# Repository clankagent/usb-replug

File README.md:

# USB Replug — revision B

A USB-A male-to-female adapter intended to simulate unplugging and reconnecting a USB 2.0 peripheral with one button press. A CMOS 555 provides the delay; there is no microcontroller or firmware.

**Public design review. Unbuilt prototype; not ready to order.** Assembly placement mappings remain unresolved and hardware performance has not been tested. This repository contains only the current revision B source and review material, not previous design iterations or fabrication releases.

[Schematic PDF](docs/schematic.pdf) · [3D STEP model](docs/usb-replug.step) · [BOM](bom.csv) · [Remaining work](docs/STATUS.md)

## Intended operation

Press the central button to disconnect device VBUS and both data lines, then reconnect automatically. Ground and shields stay connected. The trigger circuit is intended to let the timer expire even when the button remains held down.

| Two-position DIP switch | Approximate off time |
|---|---:|
| Both OFF | 3 seconds |
| Either ON | 2 seconds |
| Both ON | 1 second |

Change the DIP settings while idle. RC tolerance, leakage and capacitor bias affect timing; these are nominal settings, not calibrated delays.

## Open the design

Open `usb-replug.kicad_pro` in KiCad 10. The root schematic links three functional sheets. The PCB, footprints and referenced STEP models are included with project-relative paths. Official symbols are embedded in the schematics; the custom symbol library is under `libraries/`.

The board is 70 × 30 mm with four copper layers and nominal 1.6 mm thickness. Its fabrication target is JLC04161H-7628, outer 1 oz / inner 0.5 oz copper, green mask, white silkscreen and lead-free HASL. The male connector overhangs the PCB edge. A different manufacturer needs a stackup and assembly review.

## Validation

The packaged source was checked with KiCad 10.0.6: no reported ERC, PCB DRC, unconnected-item or schematic-parity findings. Reports and their configured ignored-check lists are included in `docs/checks/`. This is not a claim that every possible rule is enabled or that hardware works.

The intended USB data rate is up to 480 Mbps. Signal integrity, impedance, interoperability, ESD behavior, loaded voltage drop and timing still require review and physical testing. Length matching alone does not validate the USB routing; the layout includes uncoupled breakout sections. A self-powered peripheral may disconnect logically without actually power-cycling. Host power budget includes the adapter's own consumption.

## Assembly and availability

All small components are intended for factory assembly. JLCPCB's quoted Economic option excluded J1, the male connector; it has accessible surface-mount signal joints plus shell mounting joints. J2 is through-hole. The quoted Standard option included both connectors. Historical September 2026 batch estimates were $71.08 and $106.07 respectively for five PCBs with two populated, excluding shipping and tax. These are not current offers or endorsements.

Gerbers and pick-and-place files are deliberately absent: the previous assembler preview exposed rotation and connector-origin mismatches. No order-ready release has been published and no board has been ordered.

## Licensing and provenance

See [THIRD_PARTY.md](THIRD_PARTY.md). Public visibility does not grant an open-source license for the original project; no project license has been selected. Existing third-party licenses remain in effect. Provenance and redistribution permissions for the imported footprints and DIP-switch model remain unresolved; see the linked notes.

Prepared with AI-assisted design and review; the KiCad files, not an image, are the design source of truth.

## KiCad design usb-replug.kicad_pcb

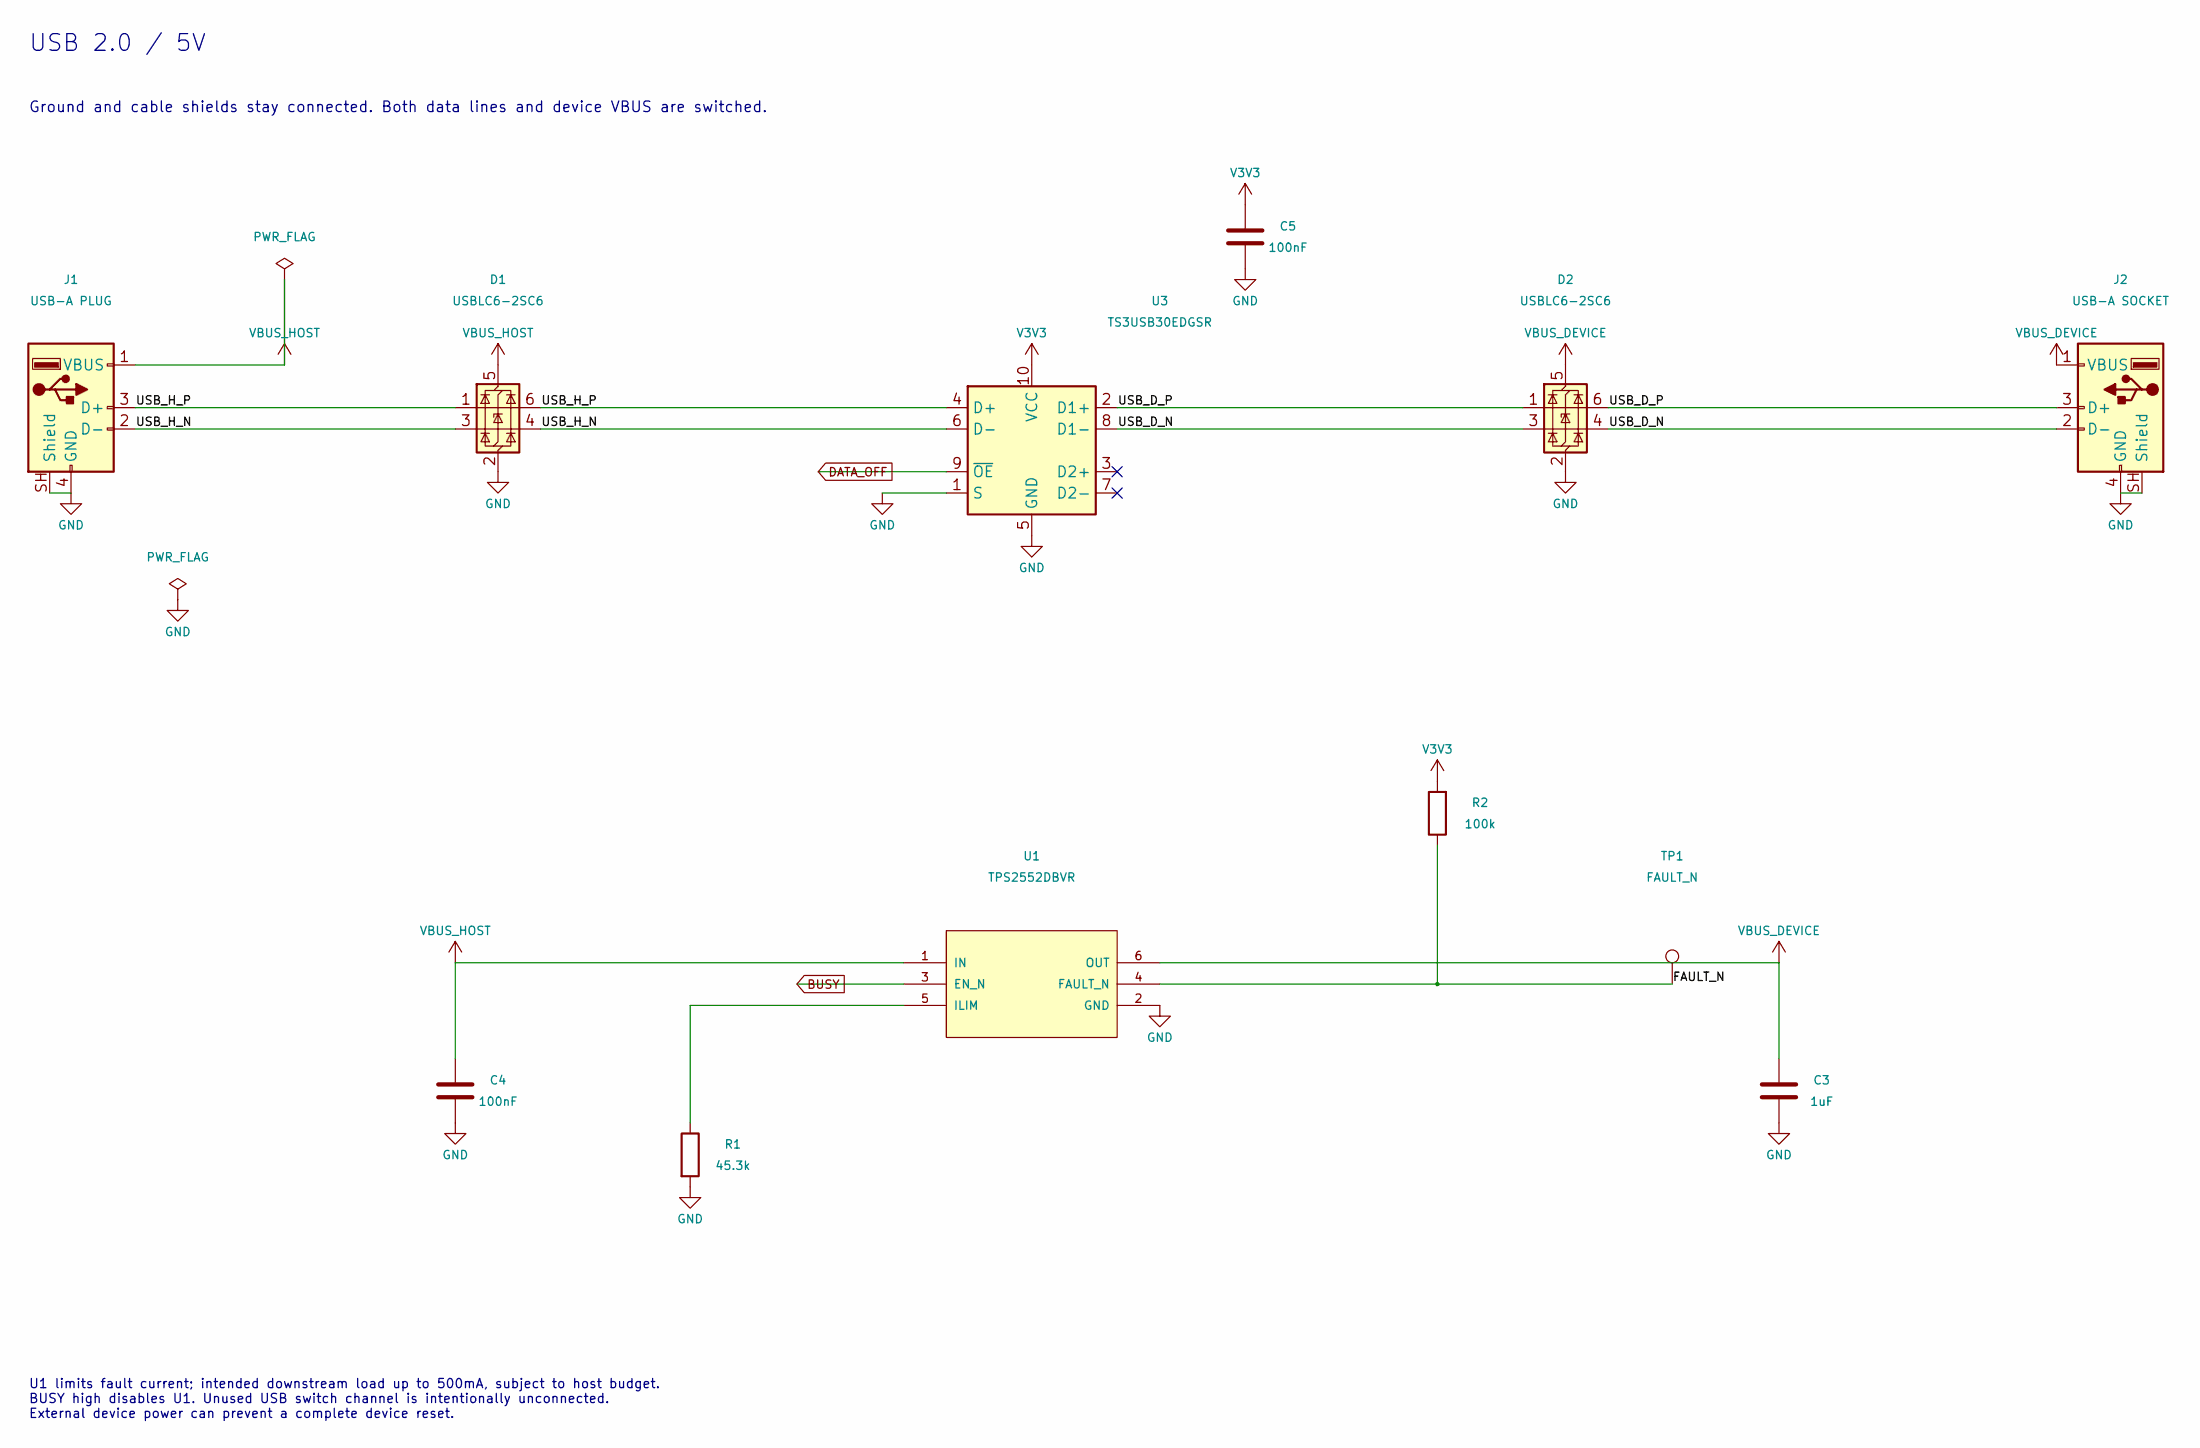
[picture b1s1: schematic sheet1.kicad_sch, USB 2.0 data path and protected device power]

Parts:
C3: 1uF; C_0603_1608Metric; MPN CL10A105KB8NNNC; LCSC C15849
C4, C5: 100nF; C_0603_1608Metric; MPN CC0603KRX7R9BB104; LCSC C14663
D1, D2: USBLC6-2SC6; SOT-23-6; MPN USBLC6-2SC6; LCSC C7519
J1: USB-A PLUG; USB_A_Molex_48037-2200_Horizontal; MPN 480372200; LCSC C2765195
J2: USB-A SOCKET; Jingtuo_902-131A1011D10100; MPN 902-131A1011D10100; LCSC C2345
R1: 45.3k; R_0603_1608Metric; MPN RC0603FR-0745K3L; LCSC C245971
R2: 100k; R_0603_1608Metric; MPN 0603WAF1003T5E; LCSC C25803
TP1: FAULT_N; TestPoint_Pad_D1.5mm; MPN PCB pad
U1: TPS2552DBVR; SOT-23-6; MPN TPS2552DBVR; LCSC C46506
U3: TS3USB30EDGSR; MSOP-10_3x3mm_P0.5mm; MPN TS3USB30EDGSR; LCSC C131998

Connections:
/USB and protected power/FAULT_N: R2.1, TP1.1, U1.4 (FAULT_N)
/USB and protected power/USB_D_N: D2.3 (I/O2), D2.4 (I/O2), J2.2 (D-), U3.8 (D1-)
/USB and protected power/USB_D_P: D2.1 (I/O1), D2.6 (I/O1), J2.3 (D+), U3.2 (D1+)
/USB and protected power/USB_H_N: D1.3 (I/O2), D1.4 (I/O2), J1.2 (D-), U3.6 (D-)
/USB and protected power/USB_H_P: D1.1 (I/O1), D1.6 (I/O1), J1.3 (D+), U3.4 (D+)
BUSY: U1.3 (EN_N); also elsewhere on the board
DATA_OFF: U3.9 (~OE); also elsewhere on the board
GND: C3.2, C4.2, C5.2, D1.2 (GND), D2.2 (GND), J1.4 (GND), J1.SH (Shield), J2.4 (GND), J2.SH (Shield), R1.2, U1.2 (GND), U3.1 (S), U3.5 (GND); also elsewhere on the board
unnamed: R1.1, U1.5 (ILIM)
V3V3: C5.1, R2.2, U3.10 (VCC); also elsewhere on the board
VBUS_DEVICE: C3.1, D2.5 (VBUS), J2.1 (VBUS), U1.6 (OUT); also elsewhere on the board
VBUS_HOST: C4.1, D1.5 (VBUS), J1.1 (VBUS), U1.1 (IN); also elsewhere on the board

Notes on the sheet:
USB 2.0 / 5V
Ground and cable shields stay connected. Both data lines and device VBUS are switched.
U1 limits fault current; intended downstream load up to 500mA, subject to host budget. BUSY high disables U1. Unused USB switch channel is intentionally unconnected. External device power can prevent a complete device reset.

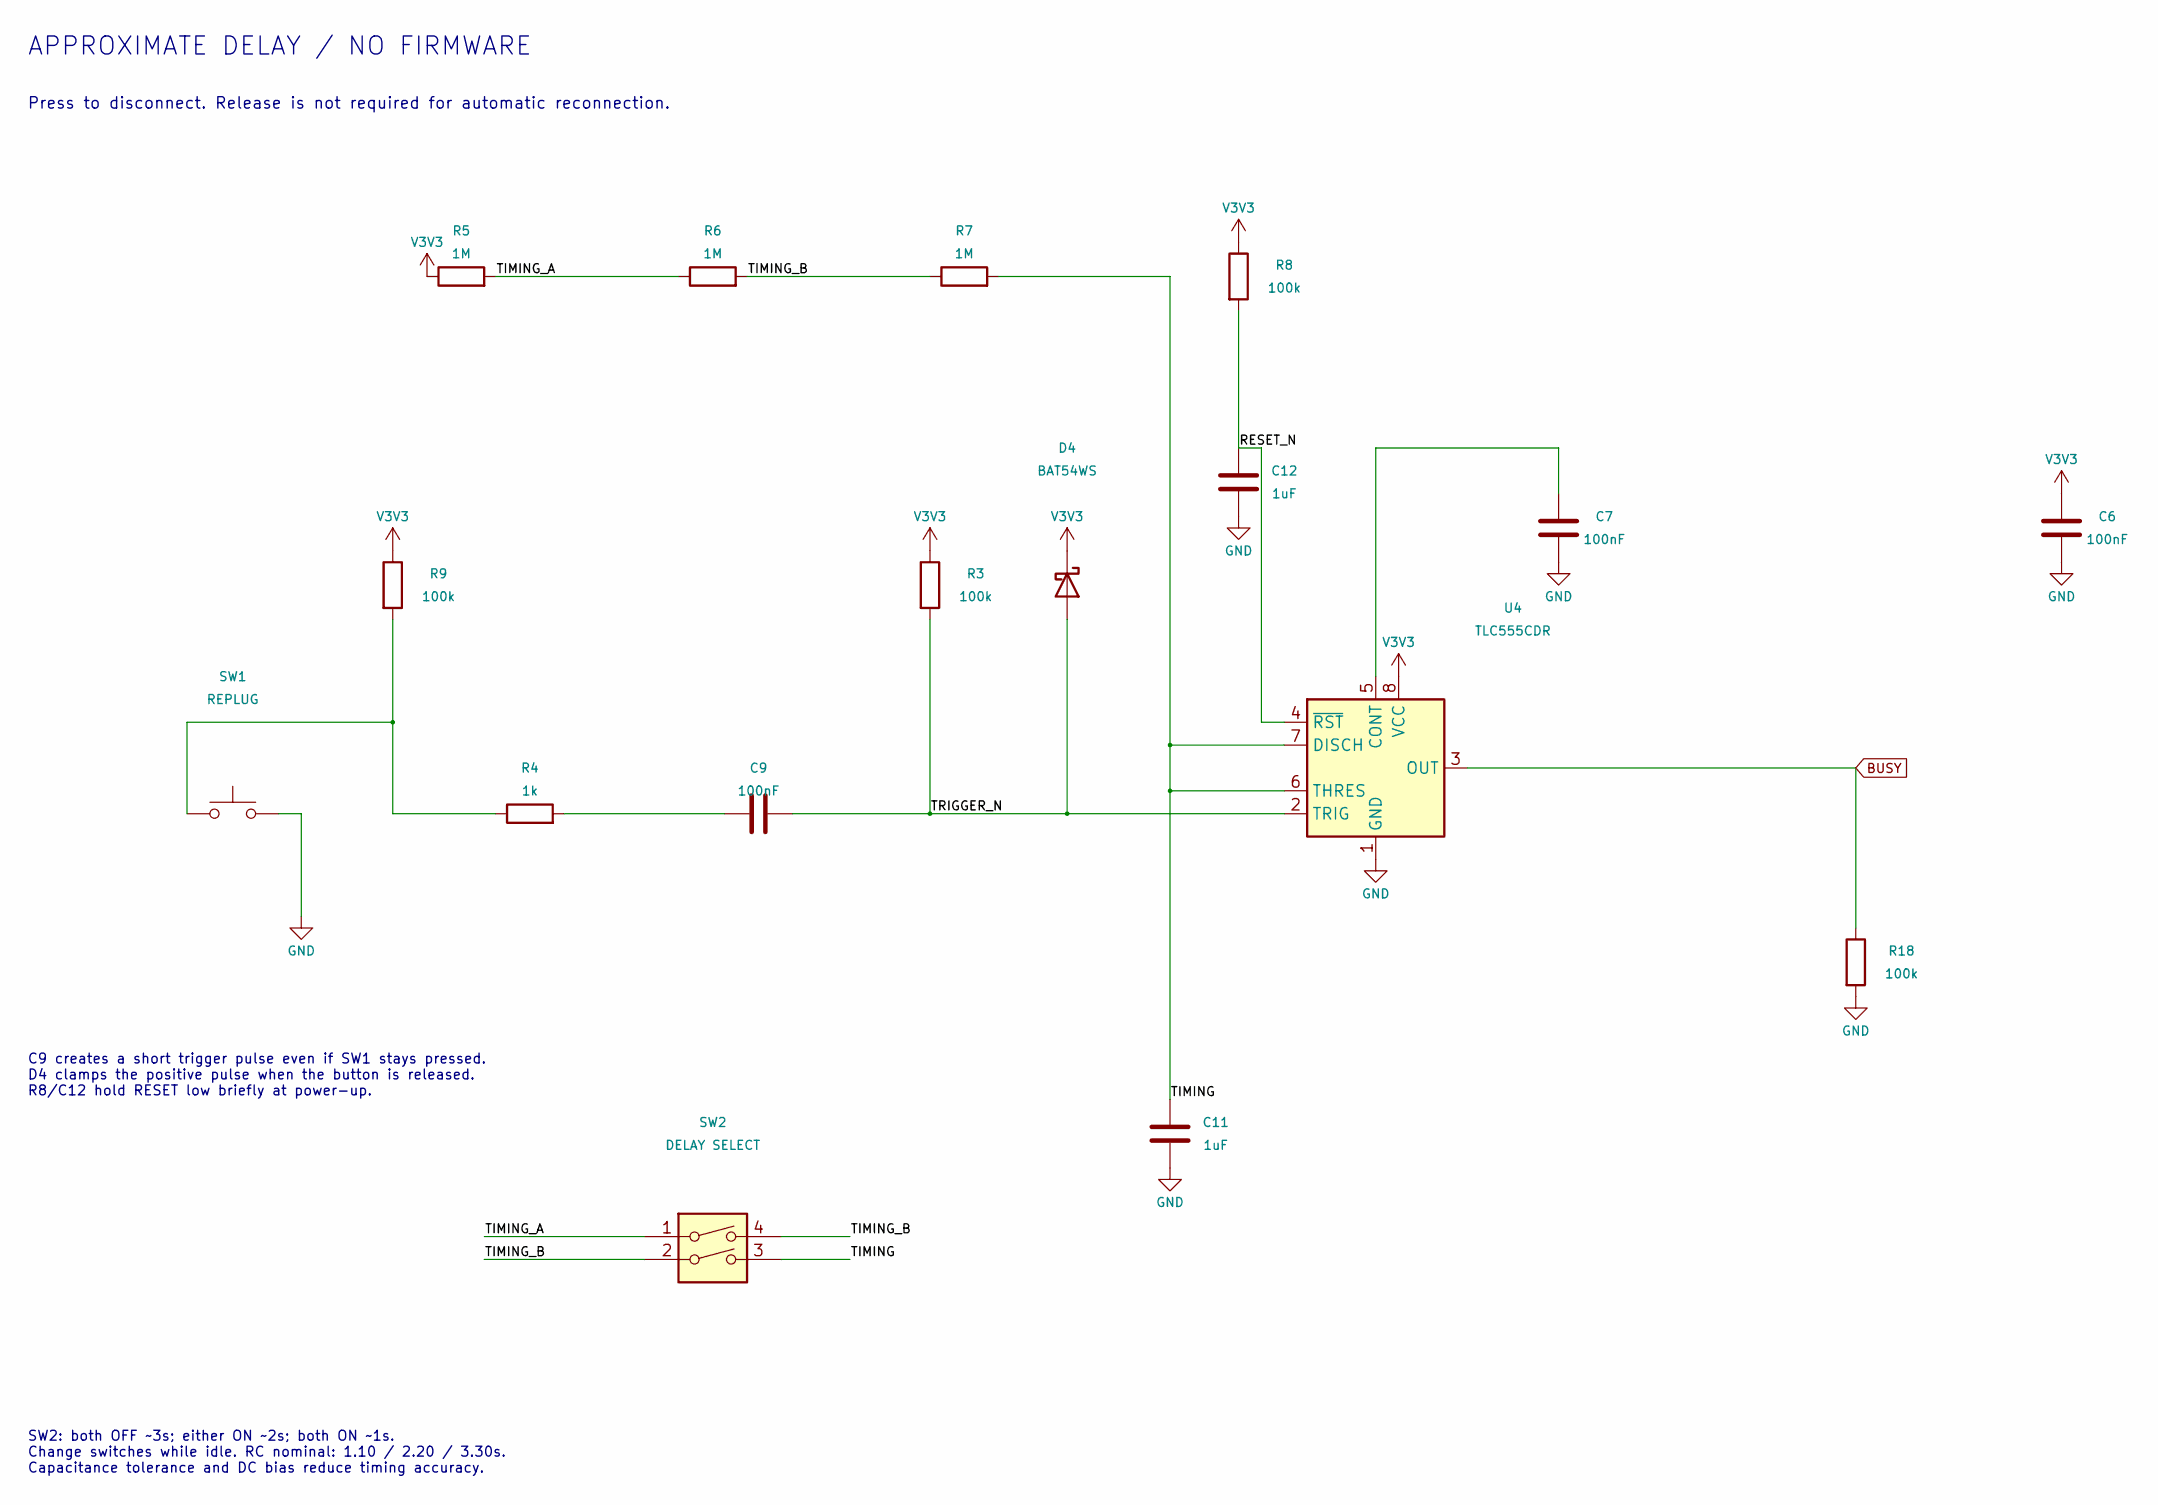
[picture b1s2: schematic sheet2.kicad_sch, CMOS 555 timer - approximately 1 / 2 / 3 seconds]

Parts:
C6, C7, C9: 100nF; C_0603_1608Metric; MPN CC0603KRX7R9BB104; LCSC C14663
C11, C12: 1uF; C_0603_1608Metric; MPN CL10A105KB8NNNC; LCSC C15849
D4: BAT54WS; D_SOD-323; MPN BAT54WS-7-F; LCSC C124205
R3, R8, R9, R18: 100k; R_0603_1608Metric; MPN 0603WAF1003T5E; LCSC C25803
R4: 1k; R_0603_1608Metric; MPN 0603WAF1001T5E; LCSC C21190
R5, R6, R7: 1M; R_0603_1608Metric; MPN 0603WAF1004T5E; LCSC C22935
SW1: REPLUG; SW_SPST_PTS645Sx43SMTR92; MPN PTS645SM43SMTR92 LFS; LCSC C221880
SW2: DELAY SELECT; SHOUHAN_1.27-2P_TPPT; MPN 1.27-2P TPPT; LCSC C7421516
U4: TLC555CDR; SOIC-8_3.9x4.9mm_P1.27mm; MPN TLC555CDR; LCSC C6986

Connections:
/555 hardware timer/RESET_N: C12.1, R8.2, U4.4 (~RST)
/555 hardware timer/TIMING: C11.1, R7.2, SW2.3, U4.6 (THRES), U4.7 (DISCH)
/555 hardware timer/TIMING_A: R5.2, R6.1, SW2.1
/555 hardware timer/TIMING_B: R6.2, R7.1, SW2.2, SW2.4
/555 hardware timer/TRIGGER_N: C9.2, D4.2 (A), R3.2, U4.2 (TRIG)
BUSY: R18.1, U4.3 (OUT); also elsewhere on the board
GND: C6.2, C7.2, C11.2, C12.2, R18.2, SW1.2, U4.1 (GND); also elsewhere on the board
unnamed: C9.1, R4.2
unnamed: R4.1, R9.2, SW1.1
unnamed: C7.1, U4.5 (CONT)
V3V3: C6.1, D4.1 (K), R3.1, R5.1, R8.1, R9.1, U4.8 (VCC); also elsewhere on the board

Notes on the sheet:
APPROXIMATE DELAY / NO FIRMWARE
Press to disconnect. Release is not required for automatic reconnection.
SW2: both OFF ~3s; either ON ~2s; both ON ~1s. Change switches while idle. RC nominal: 1.10 / 2.20 / 3.30s. Capacitance tolerance and DC bias reduce timing accuracy.
C9 creates a short trigger pulse even if SW1 stays pressed. D4 clamps the positive pulse when the button is released. R8/C12 hold RESET low briefly at power-up.

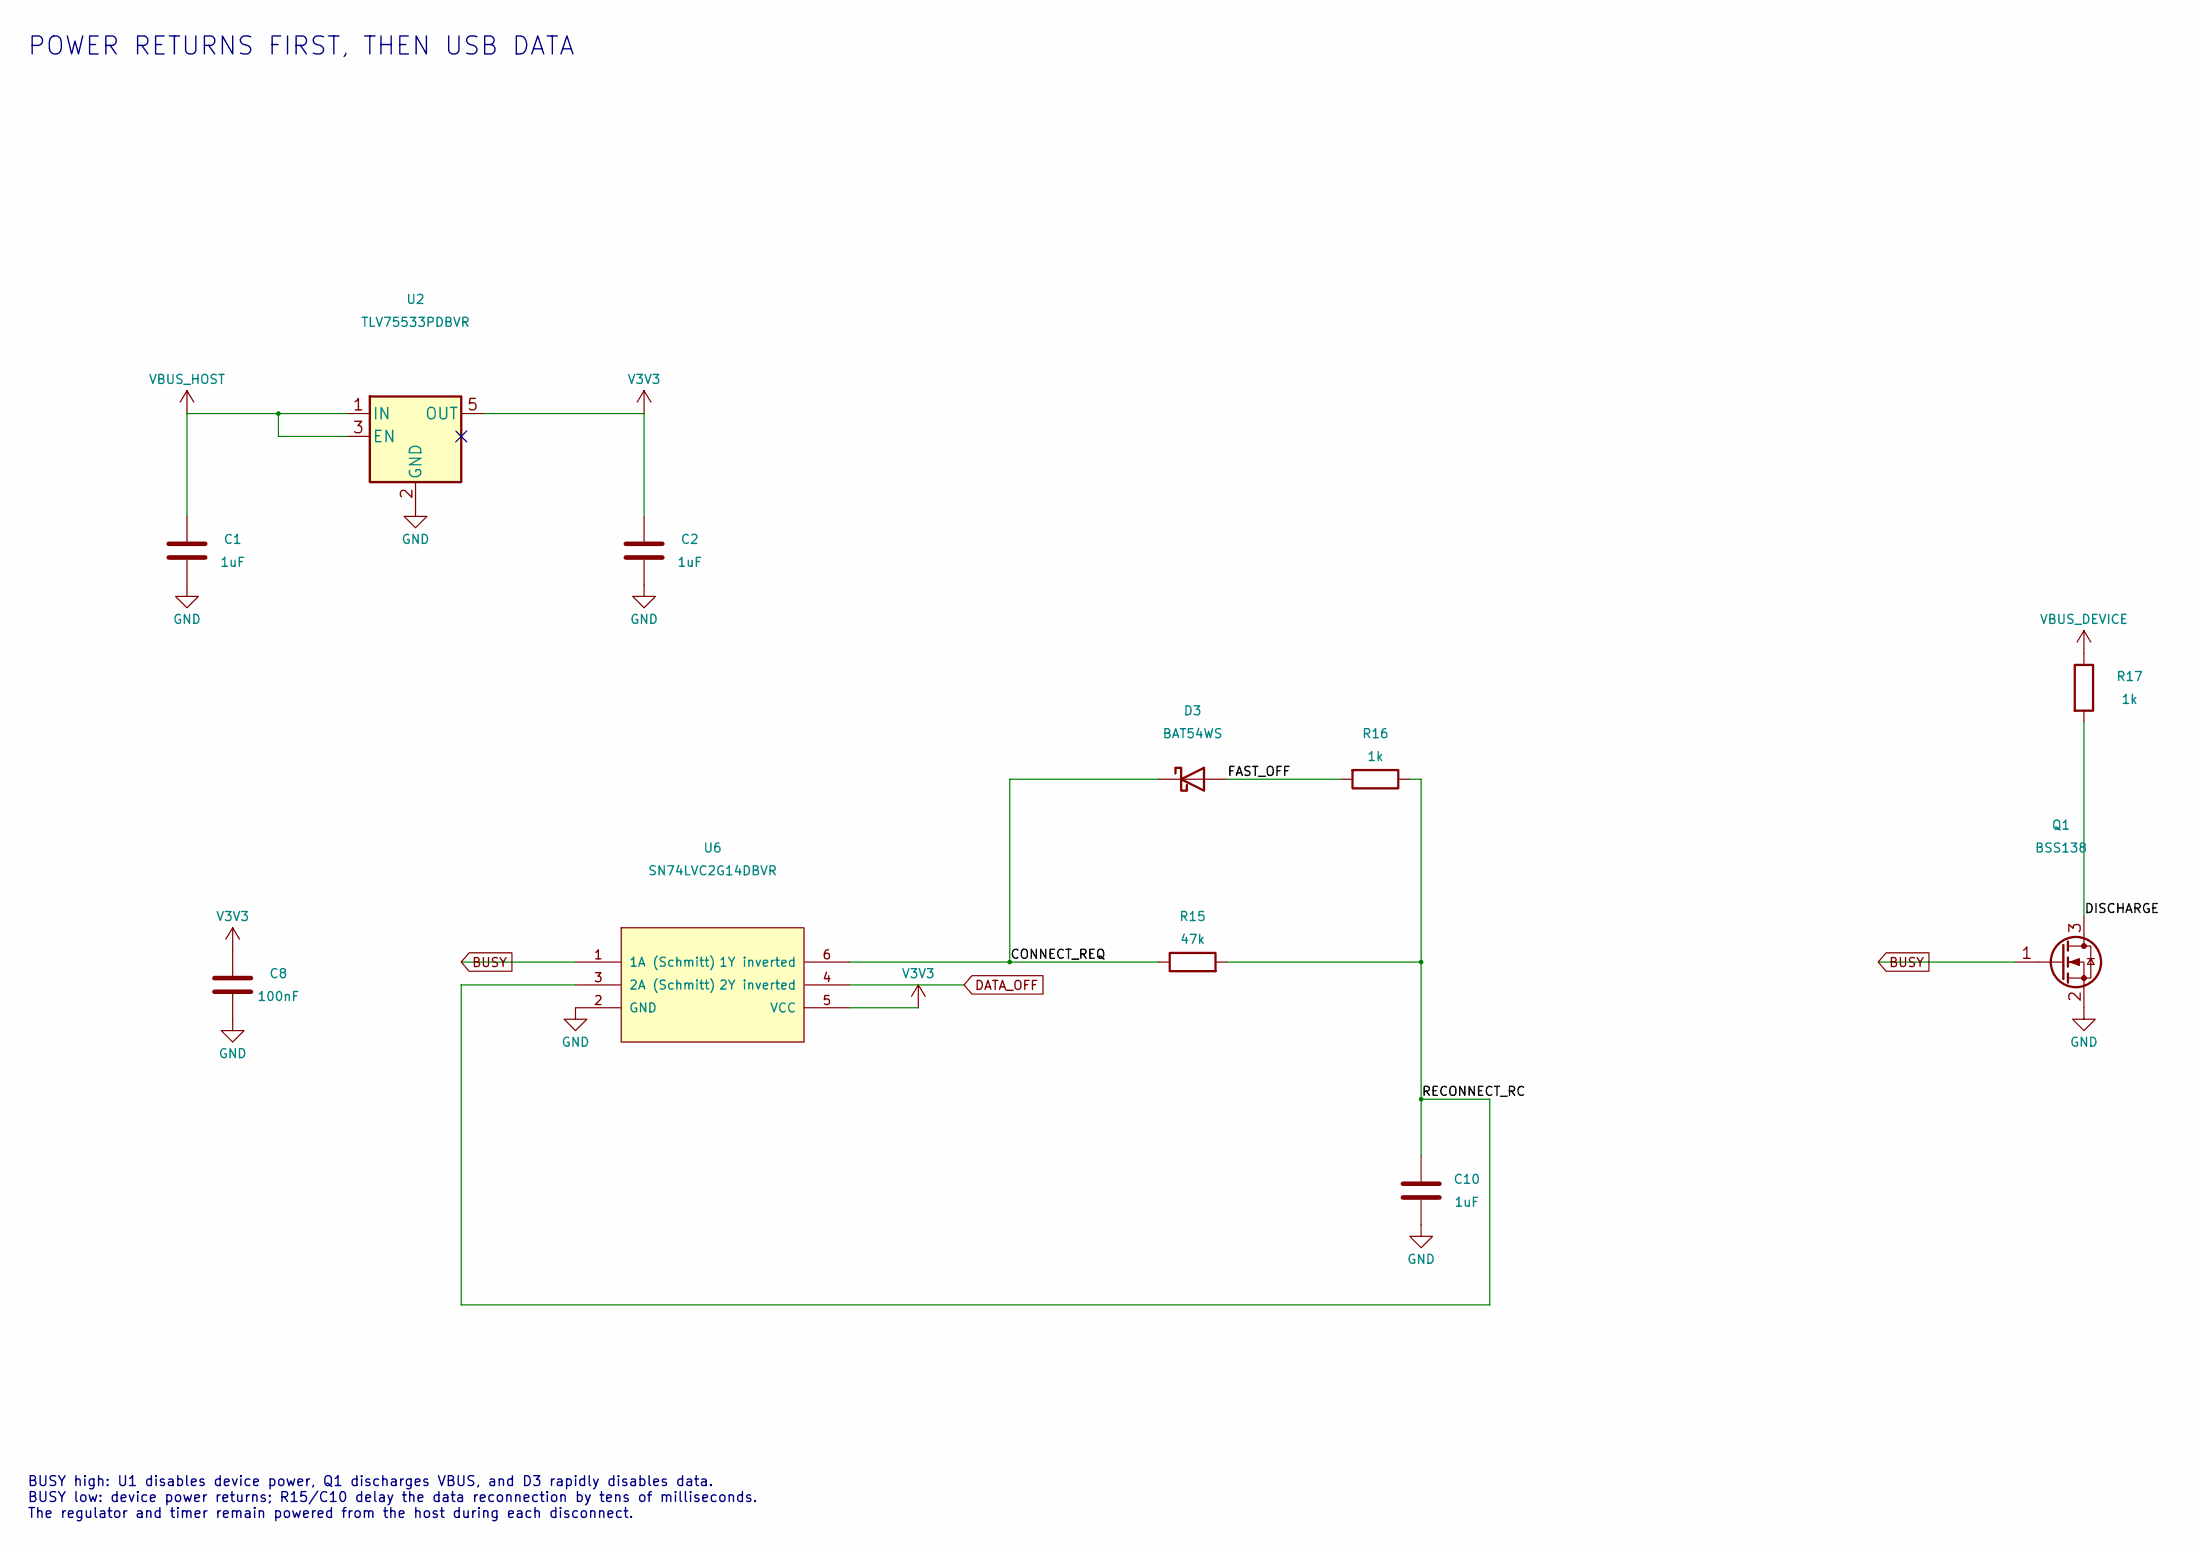
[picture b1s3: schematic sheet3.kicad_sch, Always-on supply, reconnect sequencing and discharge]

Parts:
C1, C2, C10: 1uF; C_0603_1608Metric; MPN CL10A105KB8NNNC; LCSC C15849
C8: 100nF; C_0603_1608Metric; MPN CC0603KRX7R9BB104; LCSC C14663
D3: BAT54WS; D_SOD-323; MPN BAT54WS-7-F; LCSC C124205
Q1: BSS138; SOT-23; MPN BSS138LT1G; LCSC C82045
R15: 47k; R_0603_1608Metric; MPN 0603WAF4702T5E; LCSC C25819
R16, R17: 1k; R_0603_1608Metric; MPN 0603WAF1001T5E; LCSC C21190
U2: TLV75533PDBVR; SOT-23-5; MPN TLV75533PDBVR; LCSC C404027
U6: SN74LVC2G14DBVR; SOT-23-6; MPN SN74LVC2G14DBVR; LCSC C12401

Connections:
/Supply and sequencing/CONNECT_REQ: D3.1 (K), R15.1, U6.6 (1Y inverted)
/Supply and sequencing/DISCHARGE: Q1.3 (D), R17.2
/Supply and sequencing/FAST_OFF: D3.2 (A), R16.2
/Supply and sequencing/RECONNECT_RC: C10.1, R15.2, R16.1, U6.3 (2A (Schmitt))
BUSY: Q1.1 (G), U6.1 (1A (Schmitt)); also elsewhere on the board
DATA_OFF: U6.4 (2Y inverted); also elsewhere on the board
GND: C1.2, C2.2, C8.2, C10.2, Q1.2 (S), U2.2 (GND), U6.2 (GND); also elsewhere on the board
V3V3: C2.1, C8.1, U2.5 (OUT), U6.5 (VCC); also elsewhere on the board
VBUS_DEVICE: R17.1; also elsewhere on the board
VBUS_HOST: C1.1, U2.1 (IN), U2.3 (EN); also elsewhere on the board

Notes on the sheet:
POWER RETURNS FIRST, THEN USB DATA
BUSY high: U1 disables device power, Q1 discharges VBUS, and D3 rapidly disables data. BUSY low: device power returns; R15/C10 delay the data reconnection by tens of milliseconds. The regulator and timer remain powered from the host during each disconnect.

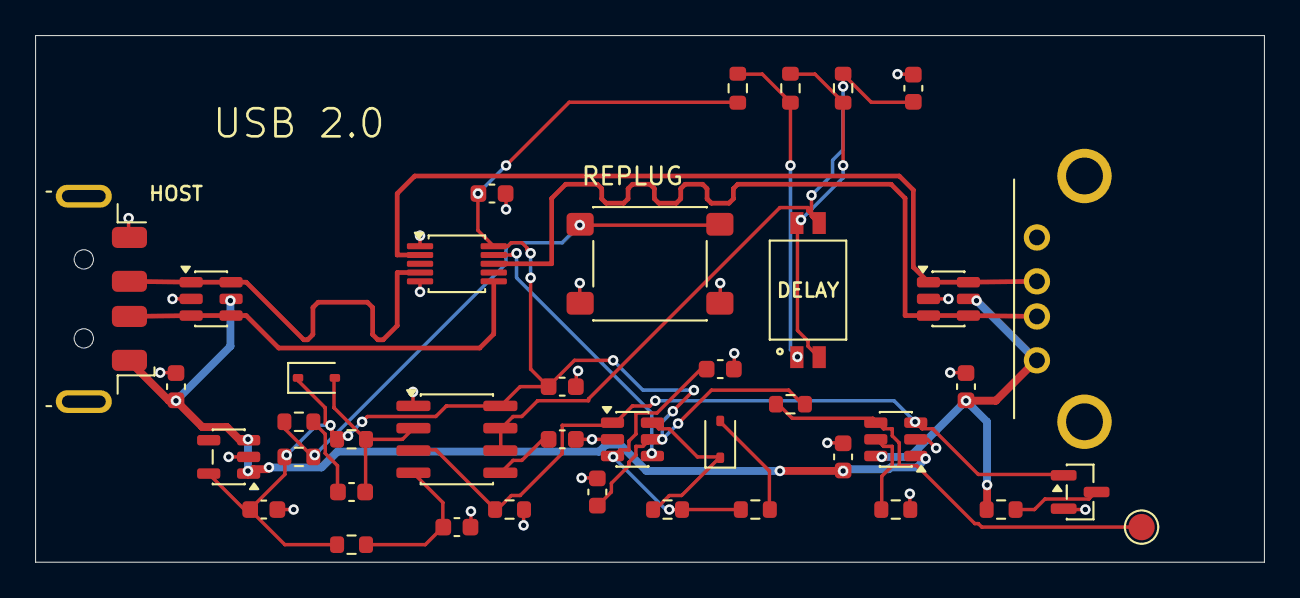
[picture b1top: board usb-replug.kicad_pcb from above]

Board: 4 copper layers, 70.0 x 30.0 mm, 40 parts (0 on the bottom side), 24 nets.

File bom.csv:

Reference,Value,Manufacturer,MPN,LCSC,Footprint,Datasheet,Notes
J1,USB-A PLUG,Molex,480372200,C2765195,Connector_USB:USB_A_Molex_48037-2200_Horizontal,https://www.molex.com/content/dam/molex/molex-dot-com/produc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,; JLCPCB Standard assembly only. Economic variant leaves this connector unpopulated.
J2,USB-A SOCKET,Jingtuo,902-131A1011D10100,C2345,ReplugB:Jingtuo_902-131A1011D10100,https://www.lcsc.com/datasheet/C2345.pdf,"USB-A female, 1.5A/30V; 0.9mm signal drills and 2.1mm shell drills per manufacturer drawing"
U1,TPS2552DBVR,Texas Instruments,TPS2552DBVR,C46506,Package_TO_SOT_SMD:SOT-23-6,https://www.ti.com/lit/ds/symlink/tps2552.pdf,
U2,TLV75533PDBVR,Texas Instruments,TLV75533PDBVR,C404027,Package_TO_SOT_SMD:SOT-23-5,https://www.ti.com/lit/ds/symlink/tlv755p.pdf,
U3,TS3USB30EDGSR,Texas Instruments,TS3USB30EDGSR,C131998,Package_SO:MSOP-10_3x3mm_P0.5mm,https://www.ti.com/lit/ds/symlink/ts3usb30e.pdf,
U4,TLC555CDR,Texas Instruments,TLC555CDR,C6986,Package_SO:SOIC-8_3.9x4.9mm_P1.27mm,https://www.ti.com/lit/ds/symlink/tlc555.pdf,CMOS monostable; C6986; no firmware; approximately 1/2/3 seconds
U6,SN74LVC2G14DBVR,Texas Instruments,SN74LVC2G14DBVR,C12401,Package_TO_SOT_SMD:SOT-23-6,https://www.ti.com/lit/ds/symlink/sn74lvc2g14.pdf,
D1,USBLC6-2SC6,STMicroelectronics,USBLC6-2SC6,C7519,Package_TO_SOT_SMD:SOT-23-6,https://www.st.com/resource/en/datasheet/usblc6-2.pdf,
D2,USBLC6-2SC6,STMicroelectronics,USBLC6-2SC6,C7519,Package_TO_SOT_SMD:SOT-23-6,https://www.st.com/resource/en/datasheet/usblc6-2.pdf,
D3,BAT54WS,Diodes Incorporated,BAT54WS-7-F,C124205,Diode_SMD:D_SOD-323,https://www.diodes.com/datasheet/download/BAT54WS.pdf,Fast RC discharge; pin 1 cathode; SOD323 two-pin package
Q1,BSS138,onsemi,BSS138LT1G,C82045,Package_TO_SOT_SMD:SOT-23,https://www.onsemi.com/pdf/datasheet/bss138lt1-d.pdf,
SW1,REPLUG,C&K,PTS645SM43SMTR92 LFS,C221880,Button_Switch_SMD:SW_SPST_PTS645Sx43SMTR92,https://www.ckswitches.com/media/1471/pts645.pdf,
SW2,DELAY SELECT,SHOUHAN,1.27-2P TPPT,C7421516,ReplugB:SHOUHAN_1.27-2P_TPPT,https://www.lcsc.com/datasheet/C7421516.pdf,24V 25mA. Switch only while idle. OFF/OFF ~3s; one ON ~2s; both ON ~1s.
R1,45.3k,Yageo,RC0603FR-0745K3L,C245971,Resistor_SMD:R_0603_1608Metric,https://www.yageo.com/upload/media/product/productsearch/dat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,Current limit approx 0.57 A; intended device load <=500mA with host budget respected
R2,100k,UNI-ROYAL,0603WAF1003T5E,C25803,Resistor_SMD:R_0603_1608Metric,https://www.lcsc.com/datasheet/C25803.pdf,"1%, 0.1 W, 0603"
R3,100k,UNI-ROYAL,0603WAF1003T5E,C25803,Resistor_SMD:R_0603_1608Metric,https://www.lcsc.com/datasheet/C25803.pdf,"1%, 0.1 W, 0603"
R4,1k,UNI-ROYAL,0603WAF1001T5E,C21190,Resistor_SMD:R_0603_1608Metric,https://www.lcsc.com/datasheet/C21190.pdf,Limits trigger clamp current
R5,1M,UNI-ROYAL,0603WAF1004T5E,C22935,Resistor_SMD:R_0603_1608Metric,https://www.lcsc.com/datasheet/C22935.pdf,"1%, 0603; t nominal = ln(3) RC; timing accuracy intentionally approximate"
R6,1M,UNI-ROYAL,0603WAF1004T5E,C22935,Resistor_SMD:R_0603_1608Metric,https://www.lcsc.com/datasheet/C22935.pdf,"1%, 0603; t nominal = ln(3) RC; timing accuracy intentionally approximate"
R7,1M,UNI-ROYAL,0603WAF1004T5E,C22935,Resistor_SMD:R_0603_1608Metric,https://www.lcsc.com/datasheet/C22935.pdf,"1%, 0603; t nominal = ln(3) RC; timing accuracy intentionally approximate"
R8,100k,UNI-ROYAL,0603WAF1003T5E,C25803,Resistor_SMD:R_0603_1608Metric,https://www.lcsc.com/datasheet/C25803.pdf,Power-on reset pull-up
R9,100k,UNI-ROYAL,0603WAF1003T5E,C25803,Resistor_SMD:R_0603_1608Metric,https://www.lcsc.com/datasheet/C25803.pdf,Button pull-up
R15,47k,UNI-ROYAL,0603WAF4702T5E,C25819,Resistor_SMD:R_0603_1608Metric,https://www.lcsc.com/datasheet/C25819.pdf,"1%, 0.1 W, 0603"
R16,1k,UNI-ROYAL,0603WAF1001T5E,C21190,Resistor_SMD:R_0603_1608Metric,https://www.lcsc.com/datasheet/C21190.pdf,"1%, 0.1 W, 0603"
R17,1k,UNI-ROYAL,0603WAF1001T5E,C21190,Resistor_SMD:R_0603_1608Metric,https://www.lcsc.com/datasheet/C21190.pdf,"1%, 0.1 W, 0603"
R18,100k,UNI-ROYAL,0603WAF1003T5E,C25803,Resistor_SMD:R_0603_1608Metric,https://www.lcsc.com/datasheet/C25803.pdf,"1%, 0.1 W, 0603"
C1,1uF,Samsung Electro-Mechanics,CL10A105KB8NNNC,C15849,Capacitor_SMD:C_0603_1608Metric,https://www.lcsc.com/datasheet/C15849.pdf,"X7R, 16V, 0603; 1uF and 100nF bypass capacitors; 50V, +/-10%, X5R; supplier Basic part"
C2,1uF,Samsung Electro-Mechanics,CL10A105KB8NNNC,C15849,Capacitor_SMD:C_0603_1608Metric,https://www.lcsc.com/datasheet/C15849.pdf,"X7R, 16V, 0603; 1uF and 100nF bypass capacitors; 50V, +/-10%, X5R; supplier Basic part"
C3,1uF,Samsung Electro-Mechanics,CL10A105KB8NNNC,C15849,Capacitor_SMD:C_0603_1608Metric,https://www.lcsc.com/datasheet/C15849.pdf,"X7R, 16V, 0603; 1uF and 100nF bypass capacitors; 50V, +/-10%, X5R; supplier Basic part"
C4,100nF,YAGEO,CC0603KRX7R9BB104,C14663,Capacitor_SMD:C_0603_1608Metric,https://www.lcsc.com/datasheet/C14663.pdf,"X7R, 16V, 0603; 1uF and 100nF bypass capacitors; 50V, +/-10%, X7R; supplier Basic part"
C5,100nF,YAGEO,CC0603KRX7R9BB104,C14663,Capacitor_SMD:C_0603_1608Metric,https://www.lcsc.com/datasheet/C14663.pdf,"X7R, 16V, 0603; 1uF and 100nF bypass capacitors; 50V, +/-10%, X7R; supplier Basic part"
C6,100nF,YAGEO,CC0603KRX7R9BB104,C14663,Capacitor_SMD:C_0603_1608Metric,https://www.lcsc.com/datasheet/C14663.pdf,"X7R, 16V, 0603; 1uF and 100nF bypass capacitors; 50V, +/-10%, X7R; supplier Basic part"
C7,100nF,YAGEO,CC0603KRX7R9BB104,C14663,Capacitor_SMD:C_0603_1608Metric,https://www.lcsc.com/datasheet/C14663.pdf,"555 control-voltage bypass; 50V, +/-10%, X7R; supplier Basic part"
C8,100nF,YAGEO,CC0603KRX7R9BB104,C14663,Capacitor_SMD:C_0603_1608Metric,https://www.lcsc.com/datasheet/C14663.pdf,"X7R, 16V, 0603; 1uF and 100nF bypass capacitors; 50V, +/-10%, X7R; supplier Basic part"
C9,100nF,YAGEO,CC0603KRX7R9BB104,C14663,Capacitor_SMD:C_0603_1608Metric,https://www.lcsc.com/datasheet/C14663.pdf,"AC-coupled falling-edge trigger: reconnects even with button held; 50V, +/-10%, X7R; supplier Basic part"
C10,1uF,Samsung Electro-Mechanics,CL10A105KB8NNNC,C15849,Capacitor_SMD:C_0603_1608Metric,https://www.lcsc.com/datasheet/C15849.pdf,"X7R, 16V, 0603; 1uF and 100nF bypass capacitors; 50V, +/-10%, X5R; supplier Basic part"
TP1,FAULT_N,PCB,PCB pad,,TestPoint:TestPoint_Pad_D1.5mm,,Diagnostic pad; no purchased component
C11,1uF,Samsung Electro-Mechanics,CL10A105KB8NNNC,C15849,Capacitor_SMD:C_0603_1608Metric,https://www.lcsc.com/datasheet/C15849.pdf,"1uF X5R 50V; nominal capacitance changes with DC bias and temperature; 50V, +/-10%, X5R; supplier Basic part"
C12,1uF,Samsung Electro-Mechanics,CL10A105KB8NNNC,C15849,Capacitor_SMD:C_0603_1608Metric,https://www.lcsc.com/datasheet/C15849.pdf,"1uF X5R 50V; nominal capacitance changes with DC bias and temperature; 50V, +/-10%, X5R; supplier Basic part"
D4,BAT54WS,Diodes Incorporated,BAT54WS-7-F,C124205,Diode_SMD:D_SOD-323,https://www.diodes.com/datasheet/download/BAT54WS.pdf,Positive trigger clamp on button release; cathode at V3V3
